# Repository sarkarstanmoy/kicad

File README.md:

# kicad
KiCad for electornics project

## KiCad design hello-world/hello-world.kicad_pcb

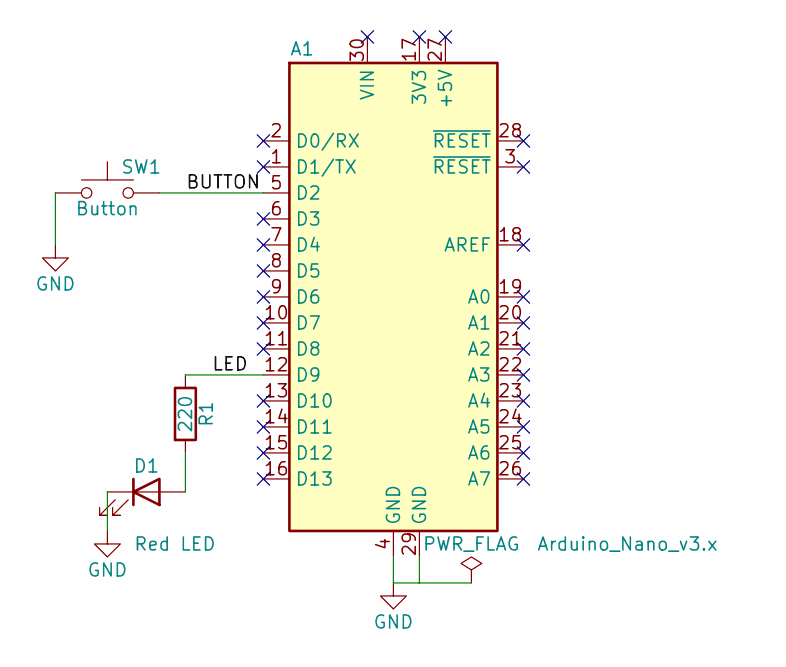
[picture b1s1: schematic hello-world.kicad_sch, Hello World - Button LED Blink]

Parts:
A1: Arduino_Nano_v3.x; Arduino_Nano
D1: Red LED; LED_D5.0mm
R1: 220; R_Axial_DIN0207_L6.3mm_D2.5mm_P10.16mm_Horizontal
SW1: Button; SW_PUSH_6mm

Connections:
/BUTTON: A1.5 (D2), SW1.2
/LED: A1.12 (D9), R1.1
GND: A1.4 (GND), A1.29 (GND), D1.1 (K), SW1.1
unnamed: D1.2 (A), R1.2

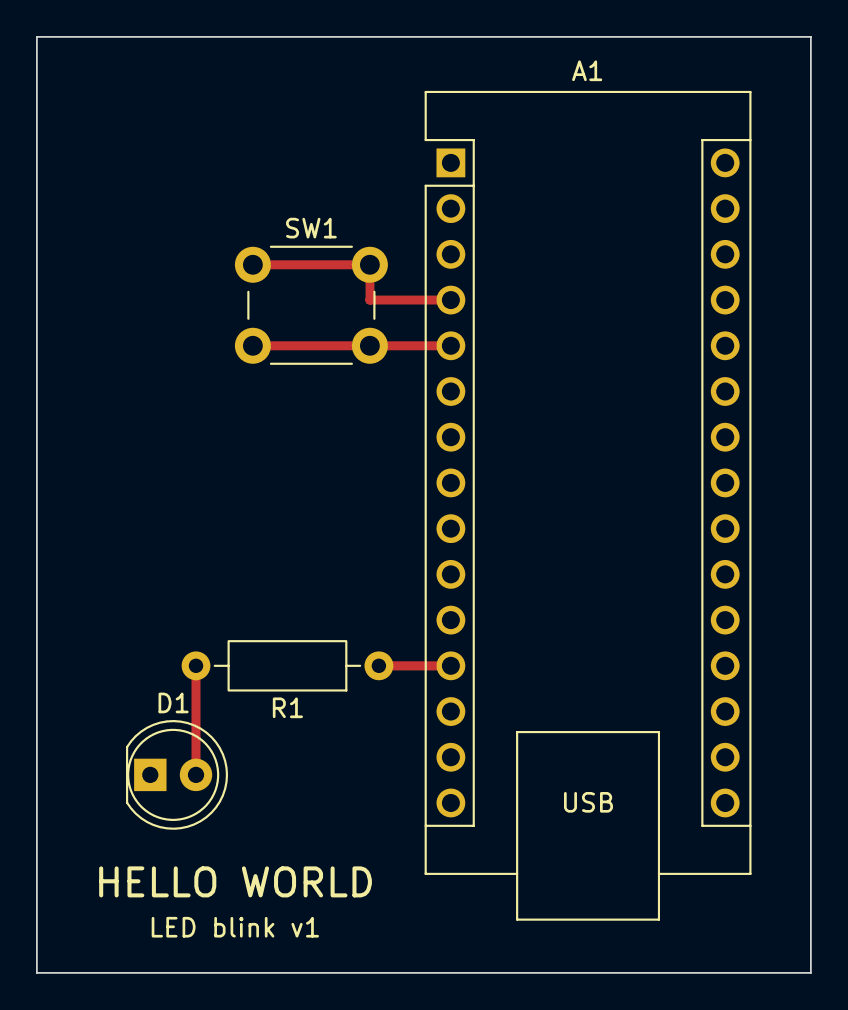
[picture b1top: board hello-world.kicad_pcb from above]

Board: 2 copper layers, 43.0 x 52.0 mm, 4 parts (0 on the bottom side), 4 nets.

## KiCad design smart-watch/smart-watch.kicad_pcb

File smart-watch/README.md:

# Smart Watch v0.1 (module build)

A beginner-friendly smartwatch built from ready-made modules, hand-wired on perfboard
with 30 AWG silicone wire. No SMD soldering needed.

| File | What it is |
|---|---|
| `smart-watch.kicad_pro` | KiCad 10 project (open this) |
| `smart-watch.kicad_sch` | Schematic: every connection, part values, supplier and price fields |
| `smart-watch.kicad_sym` / `smart-watch.pretty/` | Project library: module symbols and footprints |
| `docs/smart-watch-schematic.pdf` | Printable schematic for the workbench |
| `docs/smart-watch-bom.csv` | Bill of materials exported from the schematic |
| `smart-watch.kicad_pcb` | 2-layer carrier PCB, 62 x 46 mm, all through-hole |
| `fab/smart-watch-gerbers.zip` | Gerbers + drill file, ready to upload to JLCPCB / PCBWay |
| `docs/pcb-top.png`, `docs/pcb-bottom.png` | 3D renders of the board |

## Specifications

| | |
|---|---|
| MCU | ESP32-C3 (RISC-V 160 MHz, Wi-Fi 2.4 GHz + BLE 5) on a SuperMini board |
| Display | 0.96" SSD1306 OLED, 128x64, I2C address `0x3C` |
| Timekeeping | DS3231 RTC (±2 ppm, about ±1 min/year), I2C `0x68`, own CR1220 backup cell |
| Time sync | NTP over Wi-Fi (optional) |
| Inputs | 3 tactile buttons: Up, Select, Down. Each one wakes the watch from deep sleep |
| Battery | 3.7 V LiPo, 300–500 mAh, JST-PH 2.0 lead |
| Charging | TP4056 module, USB-C, 1 A max (DW01 over-charge, over-discharge and short protection) |
| Power switch | Slide switch between the charger output and the ESP32 |
| Battery monitor | 1:2 divider on GPIO0 (ADC1) |
| Approx. size | Stack of ~35 x 30 x 15 mm before the case |

## Pin assignments (ESP32-C3 SuperMini)

| Pin | Net | Connected to | Why this pin |
|---|---|---|---|
| 5V | VSYS | D1 cathode | Battery feeds the board's onboard 3.3 V regulator |
| 3V3 | +3V3 | OLED VCC, RTC + | Regulated 3.3 V for both I2C modules |
| GND | GND | Everything's ground, TP4056 OUT- | |
| GPIO0 | BAT_ADC | R1/R2 midpoint, C1 | ADC1 channel, still works while Wi-Fi is on |
| GPIO3 | BTN_UP | SW1 to GND | Can wake from deep sleep (GPIO0–5 only) |
| GPIO4 | BTN_SELECT | SW2 to GND | Can wake from deep sleep |
| GPIO5 | BTN_DOWN | SW3 to GND | Can wake from deep sleep |
| GPIO6 | I2C_SDA | OLED SDA, RTC D | Not a strapping pin |
| GPIO7 | I2C_SCL | OLED SCL, RTC C | Not a strapping pin |
| GPIO1, GPIO10 | (spare) | | Free for a buzzer or vibration motor later |
| GPIO2, 8, 9 | (unused) | | Strapping pins; GPIO8 drives the onboard LED, GPIO9 is BOOT |
| GPIO20, 21 | (unused) | | UART RX/TX |

> Clone boards differ. Wire by the labels printed on your modules, not by pin position.
> The OLED in particular may be `VCC GND SCL SDA` instead of `GND VCC SCL SDA`.

Firmware pin map for the Arduino IDE (board: **ESP32C3 Dev Module**, USB CDC On Boot: Enabled):

```cpp
#define PIN_BAT_ADC   0
#define PIN_BTN_UP    3
#define PIN_BTN_SEL   4
#define PIN_BTN_DOWN  5
#define PIN_SDA       6
#define PIN_SCL       7
// Wire.begin(PIN_SDA, PIN_SCL);
// Buttons: pinMode(pin, INPUT_PULLUP); pressed = LOW
// Deep sleep: esp_deep_sleep_enable_gpio_wakeup((1<<3)|(1<<4)|(1<<5), ESP_GPIO_WAKEUP_GPIO_LOW);
// Battery volts = analogReadMilliVolts(PIN_BAT_ADC) * 2 / 1000.0
```

## Wiring list

| # | From | To | Net |
|---|---|---|---|
| 1 | LiPo red (+) | TP4056 B+ | BAT+ |
| 2 | LiPo black (-) | TP4056 B- | BAT- |
| 3 | TP4056 OUT+ | Slide switch middle pin | BAT_OUT |
| 4 | Slide switch outer pin | D1 anode | VSW |
| 5 | D1 cathode (band) | ESP32 5V | VSYS |
| 6 | TP4056 OUT- | ESP32 GND | GND |
| 7 | ESP32 3V3 | OLED VCC and RTC + | +3V3 |
| 8 | ESP32 GND | OLED GND and RTC - | GND |
| 9 | ESP32 GPIO6 | OLED SDA and RTC D | I2C_SDA |
| 10 | ESP32 GPIO7 | OLED SCL and RTC C | I2C_SCL |
| 11 | ESP32 GPIO3 / 4 / 5 | One leg of SW1 / SW2 / SW3 | BTN_* |
| 12 | Other leg of each button | GND | GND |
| 13 | VSW (switch outer pin) | R1 (100k) to R2 (100k) to GND | BAT_ADC at the middle |
| 14 | R1/R2 midpoint | ESP32 GPIO0, plus C1 (100nF) to GND | BAT_ADC |

Never connect B- to OUT-: the protection chip sits between them.

## PCB (optional instead of perfboard)

| | |
|---|---|
| Size | 62 x 46 mm, 2 layers, 1.6 mm FR-4 |
| Tracks | 0.4 mm wide, 0.2 mm clearance, 6 vias (0.8 mm pad / 0.4 mm drill) |
| GND | Copper pour on both layers |
| Checks | ERC 0 violations; DRC 0 violations, 0 unconnected, matches the schematic |

Layout: TP4056 top-left (USB-C on the left edge for charging), ESP32-C3 top-right (USB-C
on the top edge for programming), battery JST, power switch and D1 in between, buttons
along the bottom. The OLED's 4-pin header sits below the ESP32. Use long pins (11 mm) so
the 27 x 27 mm OLED module stacks **over** the ESP32, header at the bottom. The display is
then upside down, so call `display.setRotation(2)`. The outline is on the `Dwgs.User` layer.

To order: upload `fab/smart-watch-gerbers.zip` to JLCPCB/PCBWay with the default settings
(2 layers, 1.6 mm, HASL). This is a module carrier, bigger than a final watch: it's for
proving the circuit before squeezing it into a case.

> Before ordering, hold your modules against a 1:1 printout of the board (KiCad: File →
> Print, scale 1:1). The ESP32-C3 SuperMini row spacing (15.24 mm) and the TP4056 pad
> positions are from typical clones and may differ on yours.

## Power budget (estimate)

| State | Current | Notes |
|---|---|---|
| Deep sleep | ~0.2 mA | ESP32 ~5 µA, regulator ~40 µA, DS3231 ~110 µA, divider ~19 µA, OLED off ~10 µA |
| Screen on, Wi-Fi off | ~30–40 mA | Short glance when a button is pressed |
| Wi-Fi time sync | ~100 mA avg, 350 mA peaks | Once a day for ~10 s |
| SuperMini red power LED | +1–2 mA always | Remove it (desolder or scrape) for real battery life |

Example day with a 400 mAh cell: deep sleep 24 h (~4.8 mAh), 30 glances of 5 s (~1.5 mAh)
and one Wi-Fi sync (~0.3 mAh) comes to about 6.6 mAh/day, so **roughly 6–8 weeks per charge**
once the power LED is removed. With the LED left on, expect about 1–2 weeks.

Low-battery limit: D1 drops ~0.2–0.3 V and the board's regulator needs ~3.4 V, so the watch
can reset during Wi-Fi bursts once the cell falls below ~3.6–3.7 V. Show a "charge me"
warning at 3.7 V. A later revision could swap D1 for a P-MOSFET "ideal diode" to recover
that headroom.

## Shopping list

The electronic parts are in `docs/smart-watch-bom.csv`. You'll also need:

| Item | Approx. price (INR) |
|---|---|
| 30 AWG silicone wire, small perfboard | 50–100 |
| 20/22 mm watch strap | 150–300 |
| 3D-printed case (Thingiverse/Printables STL, printed by Robu.in or a local service) | 200–500 |
| CR1220 cell for the DS3231 mini (if not included) | 20–40 |

Total with the modules: roughly ₹1,500–2,500. Tools (if needed): soldering iron kit,
multimeter, hot glue gun, wire stripper.

Where to buy: Robu.in, Robocraze, ElectronicsComp, Probots, Evelta, Amazon.in (check reviews),
or Chenoy Trade Centre (CTC) in Secunderabad.

## Build order

1. **Breadboard:** ESP32-C3 + OLED + RTC on I2C (GPIO6/7). Show the time using the
   `Adafruit_SSD1306` and `RTClib` libraries. Power from the ESP32's USB.
2. **Buttons and sleep:** add SW1–SW3 and deep sleep, and wake on any button.
3. **Battery:** add LiPo, TP4056, slide switch, D1 and the battery divider. Check with a
   multimeter that VSYS reads about 3.5–4.0 V **before** connecting the ESP32.
4. **Final assembly:** solder everything with thin wire, insulate with Kapton tape or heat
   shrink, fit it into the case and attach the strap.

## Safety

- Never puncture, bend, crush or short-circuit the LiPo. Keep it away from the soldering iron.
- Only use a TP4056 module **with** protection (DW01 + 8205A chips next to the B+/B- pads).
- Check battery polarity with a multimeter: some JST leads are wired backwards.
- Don't charge the watch unattended or while wearing it during the first tests.

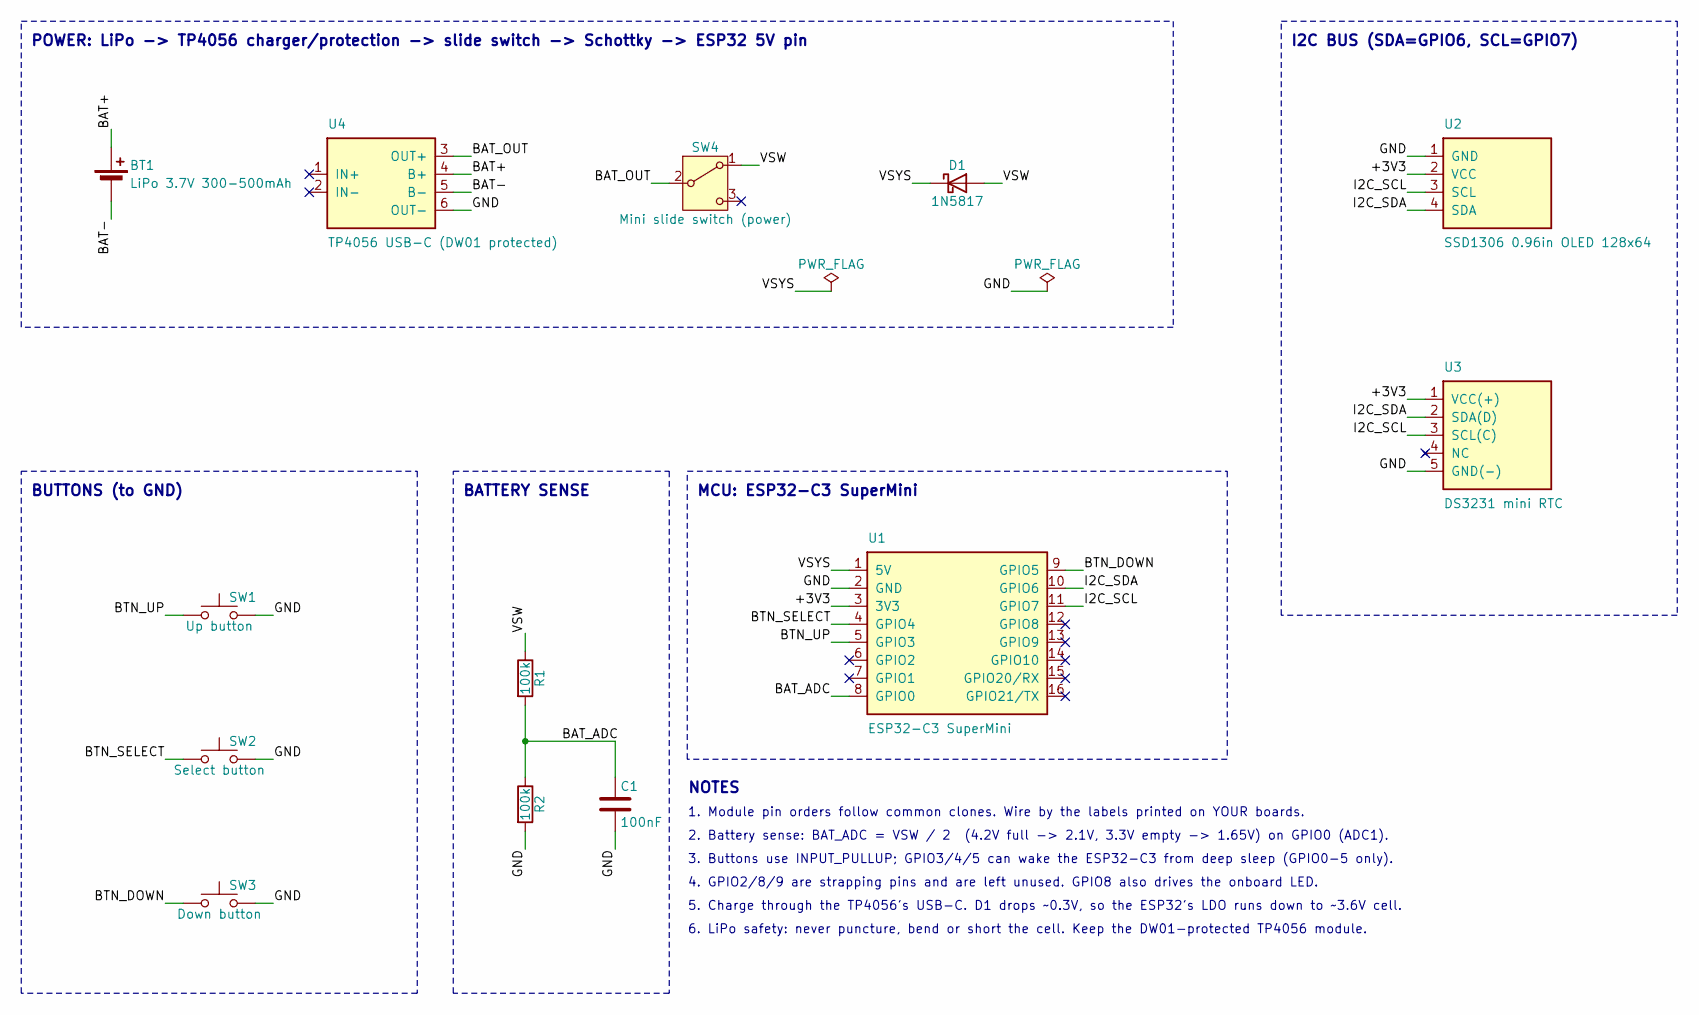
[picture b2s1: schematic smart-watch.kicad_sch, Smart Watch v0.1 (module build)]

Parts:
BT1: LiPo 3.7V 300-500mAh; JST_PH_B2B-PH-K_1x02_P2.00mm_Vertical
C1: 100nF; C_Disc_D3.0mm_W1.6mm_P2.50mm
D1: 1N5817; D_DO-41_SOD81_P10.16mm_Horizontal
R1, R2: 100k; R_Axial_DIN0207_L6.3mm_D2.5mm_P7.62mm_Horizontal
SW1: Up button; SW_PUSH_6mm
SW2: Select button; SW_PUSH_6mm
SW3: Down button; SW_PUSH_6mm
SW4: Mini slide switch (power); SW_Slide_SPDT_Straight_CK_OS102011MS2Q
U1: ESP32-C3 SuperMini; ESP32-C3_SuperMini
U2: SSD1306 0.96in OLED 128x64; PinHeader_1x04_P2.54mm_Vertical
U3: DS3231 mini RTC; PinHeader_1x05_P2.54mm_Vertical
U4: TP4056 USB-C (DW01 protected); TP4056_TypeC_Module

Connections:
/+3V3: U1.3 (3V3), U2.2 (VCC), U3.1 (VCC(+))
/BAT+: BT1.1 (+), U4.4 (B+)
/BAT-: BT1.2 (-), U4.5 (B-)
/BAT_ADC: C1.1, R1.2, R2.1, U1.8 (GPIO0)
/BAT_OUT: SW4.2 (B), U4.3 (OUT+)
/BTN_DOWN: SW3.1, U1.9 (GPIO5)
/BTN_SELECT: SW2.1, U1.4 (GPIO4)
/BTN_UP: SW1.1, U1.5 (GPIO3)
/GND: C1.2, R2.2, SW1.2, SW2.2, SW3.2, U1.2 (GND), U2.1 (GND), U3.5 (GND(-)), U4.6 (OUT-)
/I2C_SCL: U1.11 (GPIO7), U2.3 (SCL), U3.3 (SCL(C))
/I2C_SDA: U1.10 (GPIO6), U2.4 (SDA), U3.2 (SDA(D))
/VSW: D1.2 (A), R1.1, SW4.1 (A)
/VSYS: D1.1 (K), U1.1 (5V)

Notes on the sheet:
POWER: LiPo -> TP4056 charger/protection -> slide switch -> Schottky -> ESP32 5V pin
MCU: ESP32-C3 SuperMini
I2C BUS (SDA=GPIO6, SCL=GPIO7)
BUTTONS (to GND)
BATTERY SENSE
NOTES
1. Module pin orders follow common clones. Wire by the labels printed on YOUR boards.
2. Battery sense: BAT_ADC = VSW / 2 (4.2V full -> 2.1V, 3.3V empty -> 1.65V) on GPIO0 (ADC1).
3. Buttons use INPUT_PULLUP; GPIO3/4/5 can wake the ESP32-C3 from deep sleep (GPIO0-5 only).
4. GPIO2/8/9 are strapping pins and are left unused. GPIO8 also drives the onboard LED.
5. Charge through the TP4056's USB-C. D1 drops ~0.3V, so the ESP32's LDO runs down to ~3.6V cell.
6. LiPo safety: never puncture, bend or short the cell. Keep the DW01-protected TP4056 module.

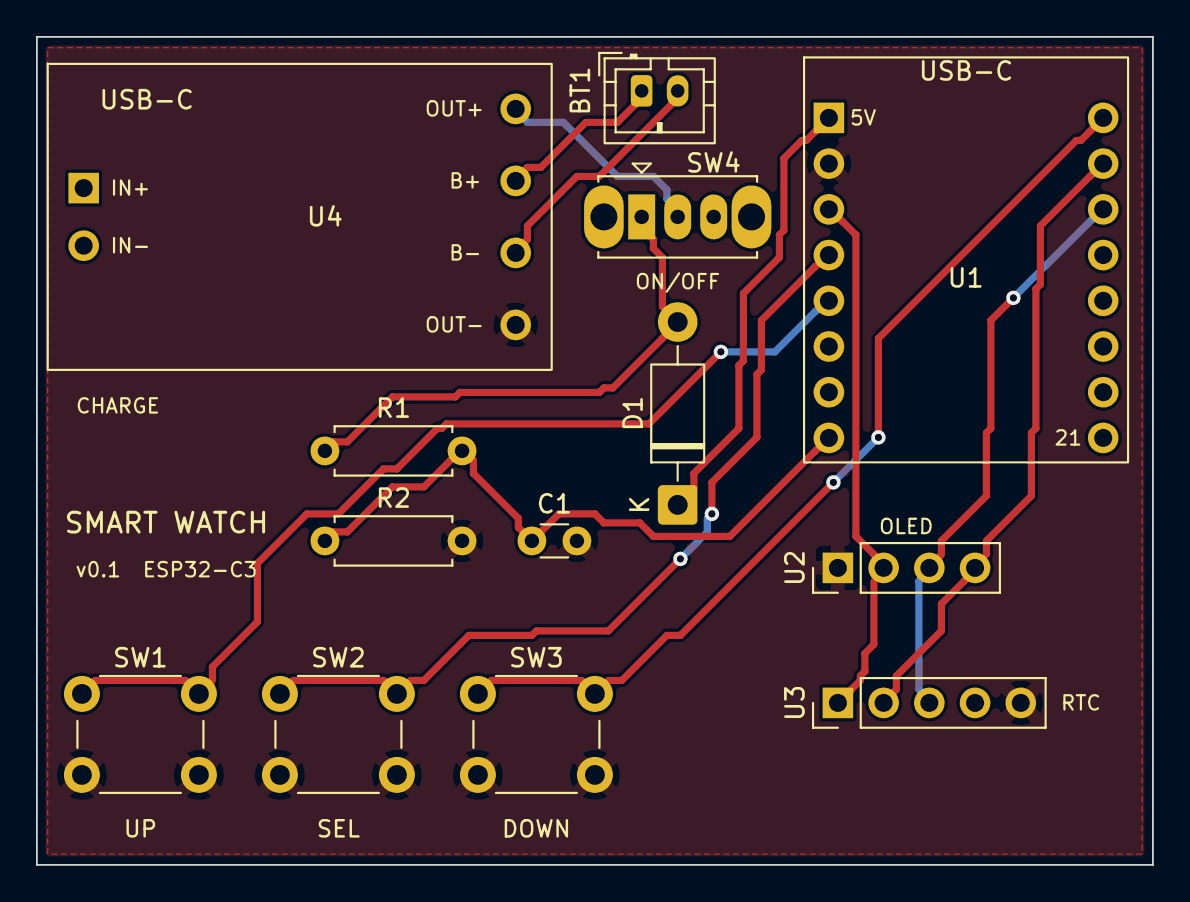
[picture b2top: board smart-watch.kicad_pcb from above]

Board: 2 copper layers, 62.0 x 46.0 mm, 13 parts (0 on the bottom side), 13 nets.
